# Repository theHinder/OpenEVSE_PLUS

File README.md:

# OpenEVSE_PLUS
README.md for OpenEVSE Hardware
Files SCH and BRD in Eagle format
License CC BY-SA 3.0
OpenEVSE Hardware

Current Version OpenEVSE_PLUS_v5.5.

OpenEVSE_PLUS_V5.5 - Moved GFCI Test pin to enable move of DC Relay outputs to PWM capable pins supporting full power closing reduced power holding in OpenEVSE 7.1.2+ firmware. Added GPIO pin pulled HIGH to auto detect board version in software to automatically set new/old pin values without requiring different firmware. Replaced 0.1" generic non-polarized connectors with JST PH for Serial (WiFi) and i2c (Display). Combined power and data connections for WiFi to reduce eliminate a screw terminal connector and simplify wiring harness. Replaced DC/DC converter with a TC1044S invert chip to generate -12v from +12v. 

OpenEVSE_PLUS_v5 - Optimized for reduced build time and high volume manufacturing of changing stations, removed most screw terminals and replaced with common connectors. Change from 2 single chanel opto-isolators for AC detection to 1 dual channel. Added ground connections to screw holes.

OpenEVSE_PLUS_v4 - Has 2 AC Detect chips like v1 + v2 plus the AC relay driver of v3. Added rectifier diodes to AC detect to improve detection in some conditions. Changed GFCI to individual pinout 4 pins.

OpenEVSE_PLUS_v3 - Removed 1 AC Detect chip and added AC relay driver. Added Current measurement circuit

OpenEVSE_PLUS_v2.5 - Added Current measurement circuit.

OpenEVSE_PLUS_v2 - modified GFCI pinout

OpenEVSE_PLUS_v1 - Inital version - Combined OpenEVSE v7 board and Advanced power supply into single board

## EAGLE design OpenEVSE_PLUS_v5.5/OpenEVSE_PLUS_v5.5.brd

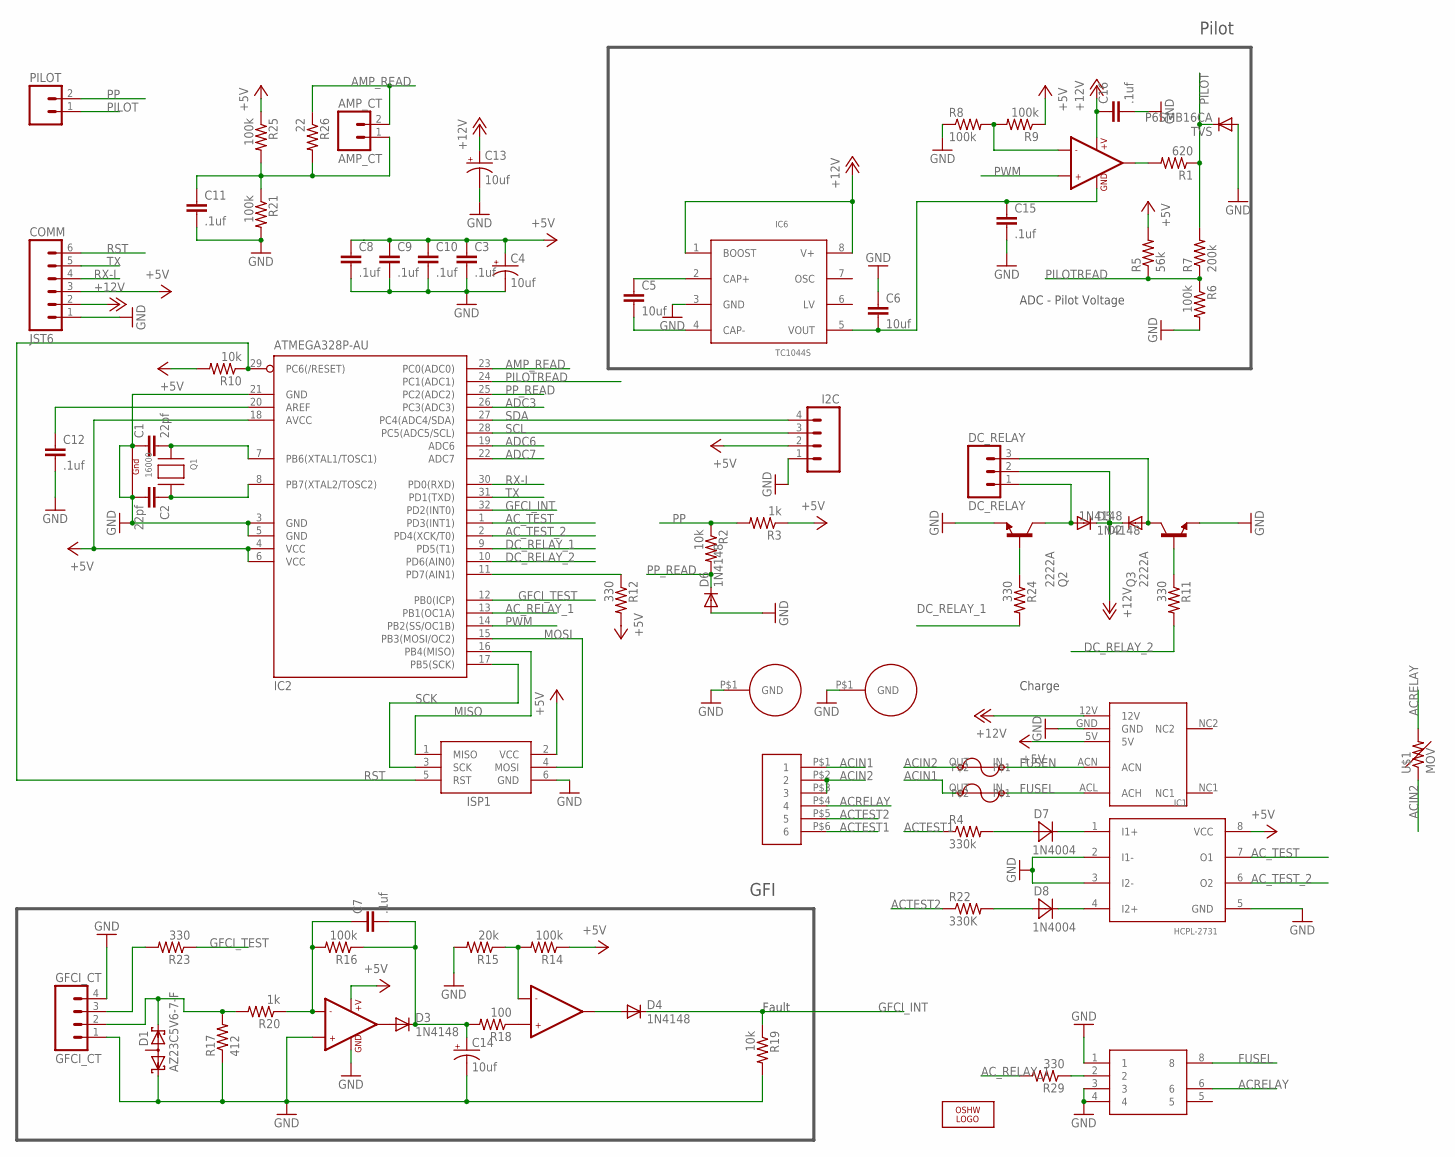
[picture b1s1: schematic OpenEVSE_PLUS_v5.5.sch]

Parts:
AC: JST-VH-6
AMP_CT: AMP_CT; MOLEX_2
C1, C2: 22pf; 0805
C3, C7, C8, C9, C10, C11, C12, C15, C16: .1uf; 0805
C4, C13, C14: 10uf; EIA3216
C5, C6: 10uf; 1206-CAP
COMM: JST6
D1: AZ23C5V6-7-F; SOT23
D2, D3, D4, D5, D6: 1N4148; SOD123
D7, D8: 1N4004; SMA
DC_RELAY: DC_RELAY; MOLEX_3
F1, F2: BEL1AFUSE; BELFUSE1A
GFCI_CT: GFCI_CT; GFCI_4
I2C: M04JST-PTH-VERT; JST-4-PTH-VERT
IC1: HCPL-2731; DIP08
IC2: ATMEGA328P-AU; TQFP32-08
IC3: LM358; SO08
IC4: LF353; SO08
IC5: AQH1213; DIP7
IC6: TC1044S; SO-8
ISP1: AVRISP-6; AVRISP
LOGO1: OSHW_LOGO_8MILX0150-NT; OSHW_8X150_NOTEXT
PILOT: M025MM; SCREWTERMINAL-5MM-2
PS1: MPM-04E-1205
Q1: 16000; NX3225
Q2, Q3: 2222A; SOT23
R1: 620; 0805
R2, R10, R19: 10k; 0805
R3, R20: 1k; 0805
R4: 330k; AXIAL-0.4
R5: 56k; 0805
R6, R8, R9, R14, R16, R21, R25: 100k; 0805
R7: 200k; 0805
R11, R12, R23, R24, R29: 330; 0805
R15: 20k; 0805
R17: 412; 0805
R18: 100; 0805
R22: 330K; AXIAL-0.4
R26: 22; 0805
TVS: P6SMB16CA; SMB
U$1: MOV
U$3, U$4: HOLE

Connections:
+5V: C3.1, C4.A (+), C8.1, C9.1, C10.1, COMM.3, I2C.2, IC1.8 (VCC), IC2.4 (VCC), IC2.6 (VCC), IC2.18 (AVCC), IC3.8 (+V), ISP1.2 (VCC), PS1.5V, R3.1, R5.2, R9.1, R10.2, R12.2, R14.1, R25.1
+12V: C13.A (+), C16.1, COMM.2, D2.C, D5.C, DC_RELAY.2, IC4.8 (+V), IC6.1 (BOOST), IC6.8 (V+), PS1.12V
-12V: C6.2, C15.1, IC4.4 (GND), IC6.5 (VOUT)
ACIN1: AC.P$1 (1), F2.OUT
ACIN2: AC.P$2 (2), AC.P$3 (3), F1.OUT, U$1.P$1 (1)
ACRELAY: AC.P$4 (4), IC5.6, U$1.P$2 (2)
ACTEST1: AC.P$6 (6), R4.P$1 (1)
ACTEST2: AC.P$5 (5), R22.P$1 (1)
AC_RELAY_1: IC2.13 (PB1(OC1A)), R29.2
AC_TEST: IC1.7 (O1), IC2.1 (PD3(INT1))
AC_TEST_2: IC1.6 (O2), IC2.2 (PD4(XCK/T0))
ADC3: IC2.26 (PC3(ADC3))
ADC6: IC2.19 (ADC6)
ADC7: IC2.22 (ADC7)
AMP_READ: AMP_CT.2, IC2.23 (PC0(ADC0)), R26.1
DC_RELAY_1: IC2.9 (PD5(T1)), R24.2
DC_RELAY_2: IC2.10 (PD6(AIN0)), R11.2
FUSEL: F2.IN, IC5.8, PS1.ACL (ACH)
FUSEN: F1.IN, PS1.ACN
GFCI_INT: D4.C, IC2.32 (PD2(INT0)), R19.1
GFCI_TEST: IC2.12 (PB0(ICP)), R23.1
GND: C1.1, C2.2, C3.2, C4.C (-), C6.1, C8.2, C9.2, C10.2, C11.2, C12.2, C13.C (-), C14.C (-), C15.2, C16.2, COMM.1, D1.1 (K1), D6.A, GFCI_CT.1, GFCI_CT.4, I2C.1, IC1.2 (I1-), IC1.3 (I2-), IC1.5 (GND), IC2.3 (GND), IC2.5 (GND), IC2.21 (GND), IC3.3 (+IN1), IC3.4 (GND), IC5.1, IC5.3, IC5.4, IC6.3 (GND), ISP1.6 (GND), PS1.GND, Q1.1 (G1), Q1.3 (G2), Q2.2 (E), Q3.2 (E), R6.2, R8.1, R15.2, R17.1, R19.2, R21.2, TVS.A, U$3.P$1, U$4.P$1
MISO: IC2.16 (PB4(MISO)), ISP1.1 (MISO)
MOSI: IC2.15 (PB3(MOSI/OC2)), ISP1.4 (MOSI)
unnamed: D2.A, DC_RELAY.3, Q3.3 (C)
unnamed: Q3.1 (B), R11.1
unnamed: C1.2, IC2.7 (PB6(XTAL1/TOSC1)), Q1.2 (X1)
unnamed: C2.1, IC2.8 (PB7(XTAL2/TOSC2)), Q1.4 (X2)
unnamed: D5.A, DC_RELAY.1, Q2.3 (C)
unnamed: AMP_CT.1, C11.1, R21.1, R25.2, R26.2
unnamed: C7.1, IC3.2 (-IN1), R16.2, R20.1
unnamed: D7.A, R4.P$2 (2)
unnamed: IC4.2 (-IN1), R8.2, R9.2
unnamed: IC4.1 (OUT1), R1.2
unnamed: D7.C, IC1.1 (I1+)
unnamed: D8.C, IC1.4 (I2+)
unnamed: D8.A, R22.P$2 (2)
unnamed: IC5.2, R29.1
unnamed: C5.1, IC6.2 (CAP+)
unnamed: D1.2 (K2), GFCI_CT.2, R17.2, R20.2
unnamed: D3.A, IC3.1 (OUT1)
unnamed: GFCI_CT.3, R23.2
unnamed: C7.2, C14.A (+), D3.C, R16.1, R18.2
unnamed: IC3.6 (-IN2), R14.2, R15.1
unnamed: D4.A, IC3.7 (OUT2)
unnamed: IC3.5 (+IN2), R18.1
unnamed: C5.2, IC6.4 (CAP-)
unnamed: IC2.11 (PD7(AIN1)), R12.1
unnamed: Q2.1 (B), R24.1
unnamed: C12.1, IC2.20 (AREF)
PILOT: PILOT.1, R1.1, R7.2, TVS.C
PILOTREAD: IC2.24 (PC1(ADC1)), R5.1, R6.1, R7.1
PP: PILOT.2, R2.1, R3.2
PP_READ: D6.C, IC2.25 (PC2(ADC2)), R2.2
PWM: IC2.14 (PB2(SS/OC1B)), IC4.3 (+IN1)
RST: COMM.6, IC2.29 (PC6(/RESET)), ISP1.5 (RST), R10.1
RX-I: COMM.4, IC2.30 (PD0(RXD))
SCK: IC2.17 (PB5(SCK)), ISP1.3 (SCK)
SCL: I2C.3, IC2.28 (PC5(ADC5/SCL))
SDA: I2C.4, IC2.27 (PC4(ADC4/SDA))
TX: COMM.5, IC2.31 (PD1(TXD))

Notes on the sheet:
Pilot
ADC - Pilot Voltage
Charge
Fault
GFI

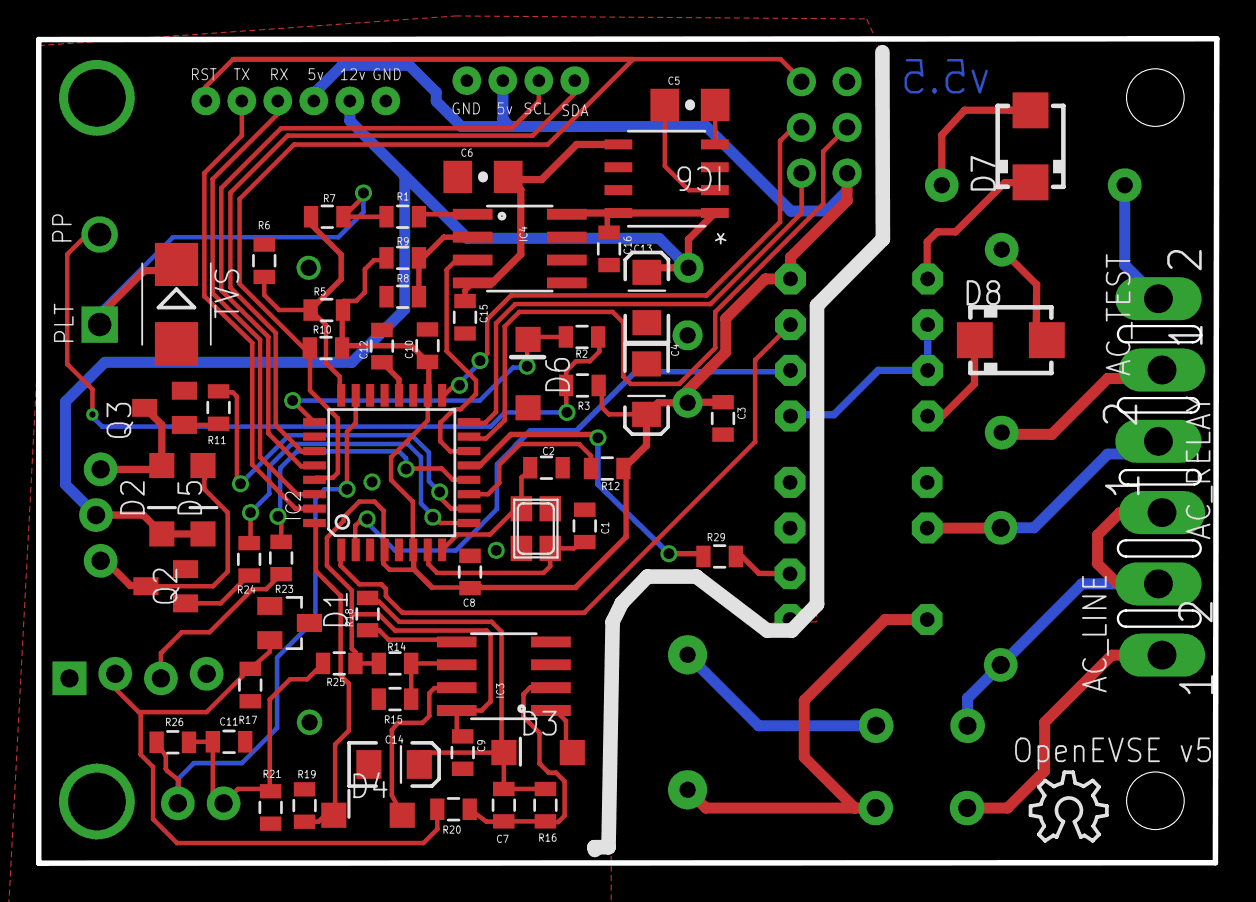
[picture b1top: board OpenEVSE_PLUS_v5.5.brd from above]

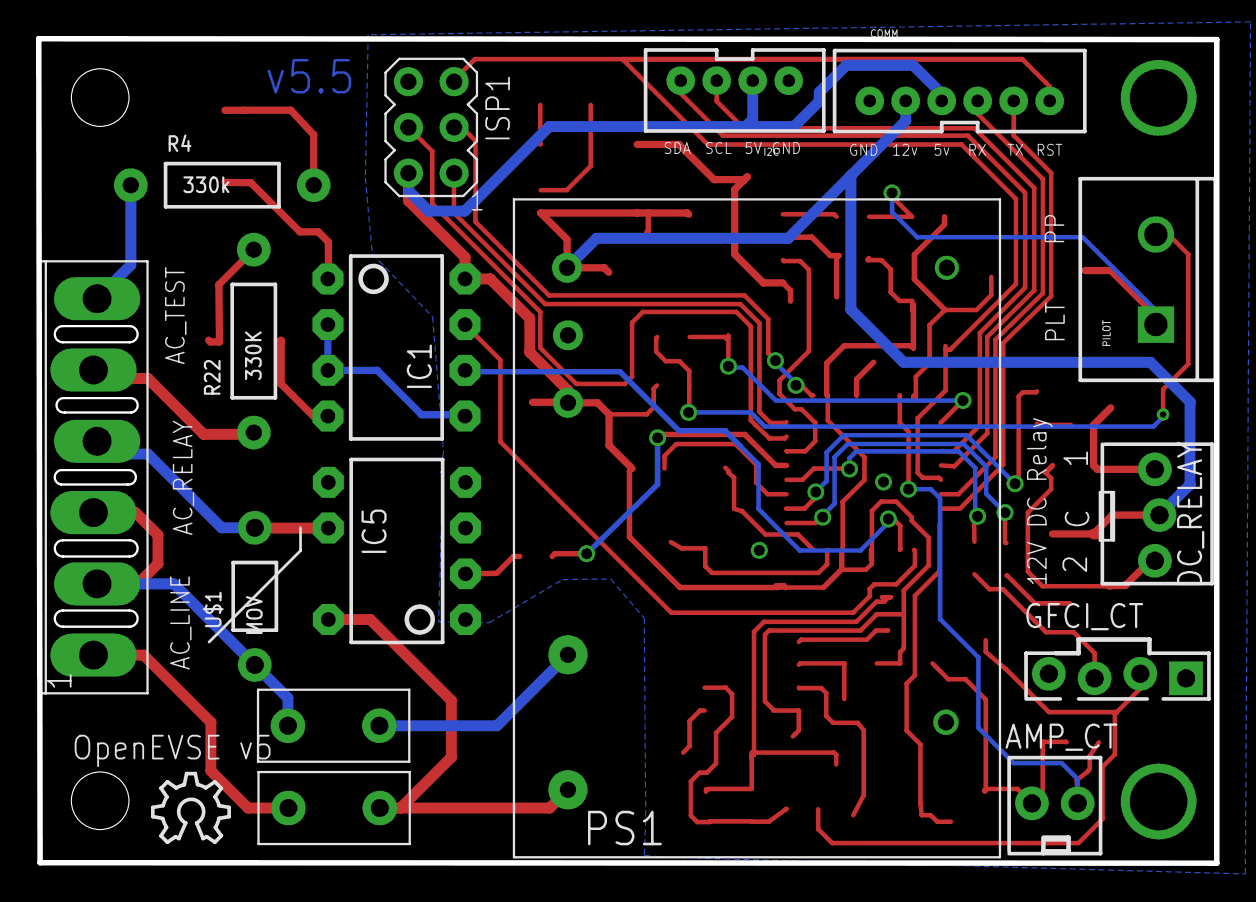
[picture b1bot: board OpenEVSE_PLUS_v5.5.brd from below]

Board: 2 copper layers, 65.4 x 45.8 mm, 76 parts (17 on the bottom side), 58 nets.

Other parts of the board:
LOGO2: OSHW_LOGO_8MILX0150-NT; OSHW_8X150_NOTEXT

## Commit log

2015-09-30 :octocat: Added .gitattributes & .gitignore files
2015-09-30 OpenEVSE_PLUS
    Move all source files from google code and web files
2015-09-30 Create README.md file
    Create file
2015-10-09 OpenEVSE Plus v1
2016-01-07 added details
2017-04-11 Updates to components
    Updated parts values so generic footprints report the correct part when exporting Eagle generated BOM.
    IC2 value 328P
    IC3 value LM358
    IC4 value LF353
    TVS value P6SMB16CA
    D1 value AZ23C5V6-7-F
2018-04-10 v5
    V5 files added
2018-04-11 v5 diagram
2018-04-23 Station Examples
    Drawing for "Standard" and "Advanced" Series. Additional drawing for 3 Phase.
2018-05-22 Add Datasheet
2018-05-22 Update Connection Diagram
    update to include part numbers for JST VH Housing and Pins and OpenEVSE GFCI and current coils
2018-10-23 Updated v5 info
2019-03-25 added pdf version of schematic
2019-03-25 changed pdf version of file name to not clash on non-case sensative operating systems
2021-01-18 Updated connection drawing
2021-04-01 Added v5.5
    Added change log for v 5.5.
2021-04-14 Upload files for OpenEVSE PLUS v 5.5
    Upload source files for OpenEVSE PLUS v 5.5
2021-06-02 Update README.md
    add TC1044S into v5.5
2021-06-02 Update README.md
    fixed typos
2021-06-02 Add files via upload
    Drawings for Advanced station and v5.5 connections
2021-06-05 Add files via upload
    JPEG
2023-06-02 Advanced_2023
    Update drawing
2024-04-03 Convert to kicad
2024-04-14 WIP new power module TMLM 04225

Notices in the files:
parts and their libraries:
SparkFun-Connectors: Licensing: Creative Commons ShareAlike 4.0 International - https://creativecommons.org/licenses/by-sa/4.0
